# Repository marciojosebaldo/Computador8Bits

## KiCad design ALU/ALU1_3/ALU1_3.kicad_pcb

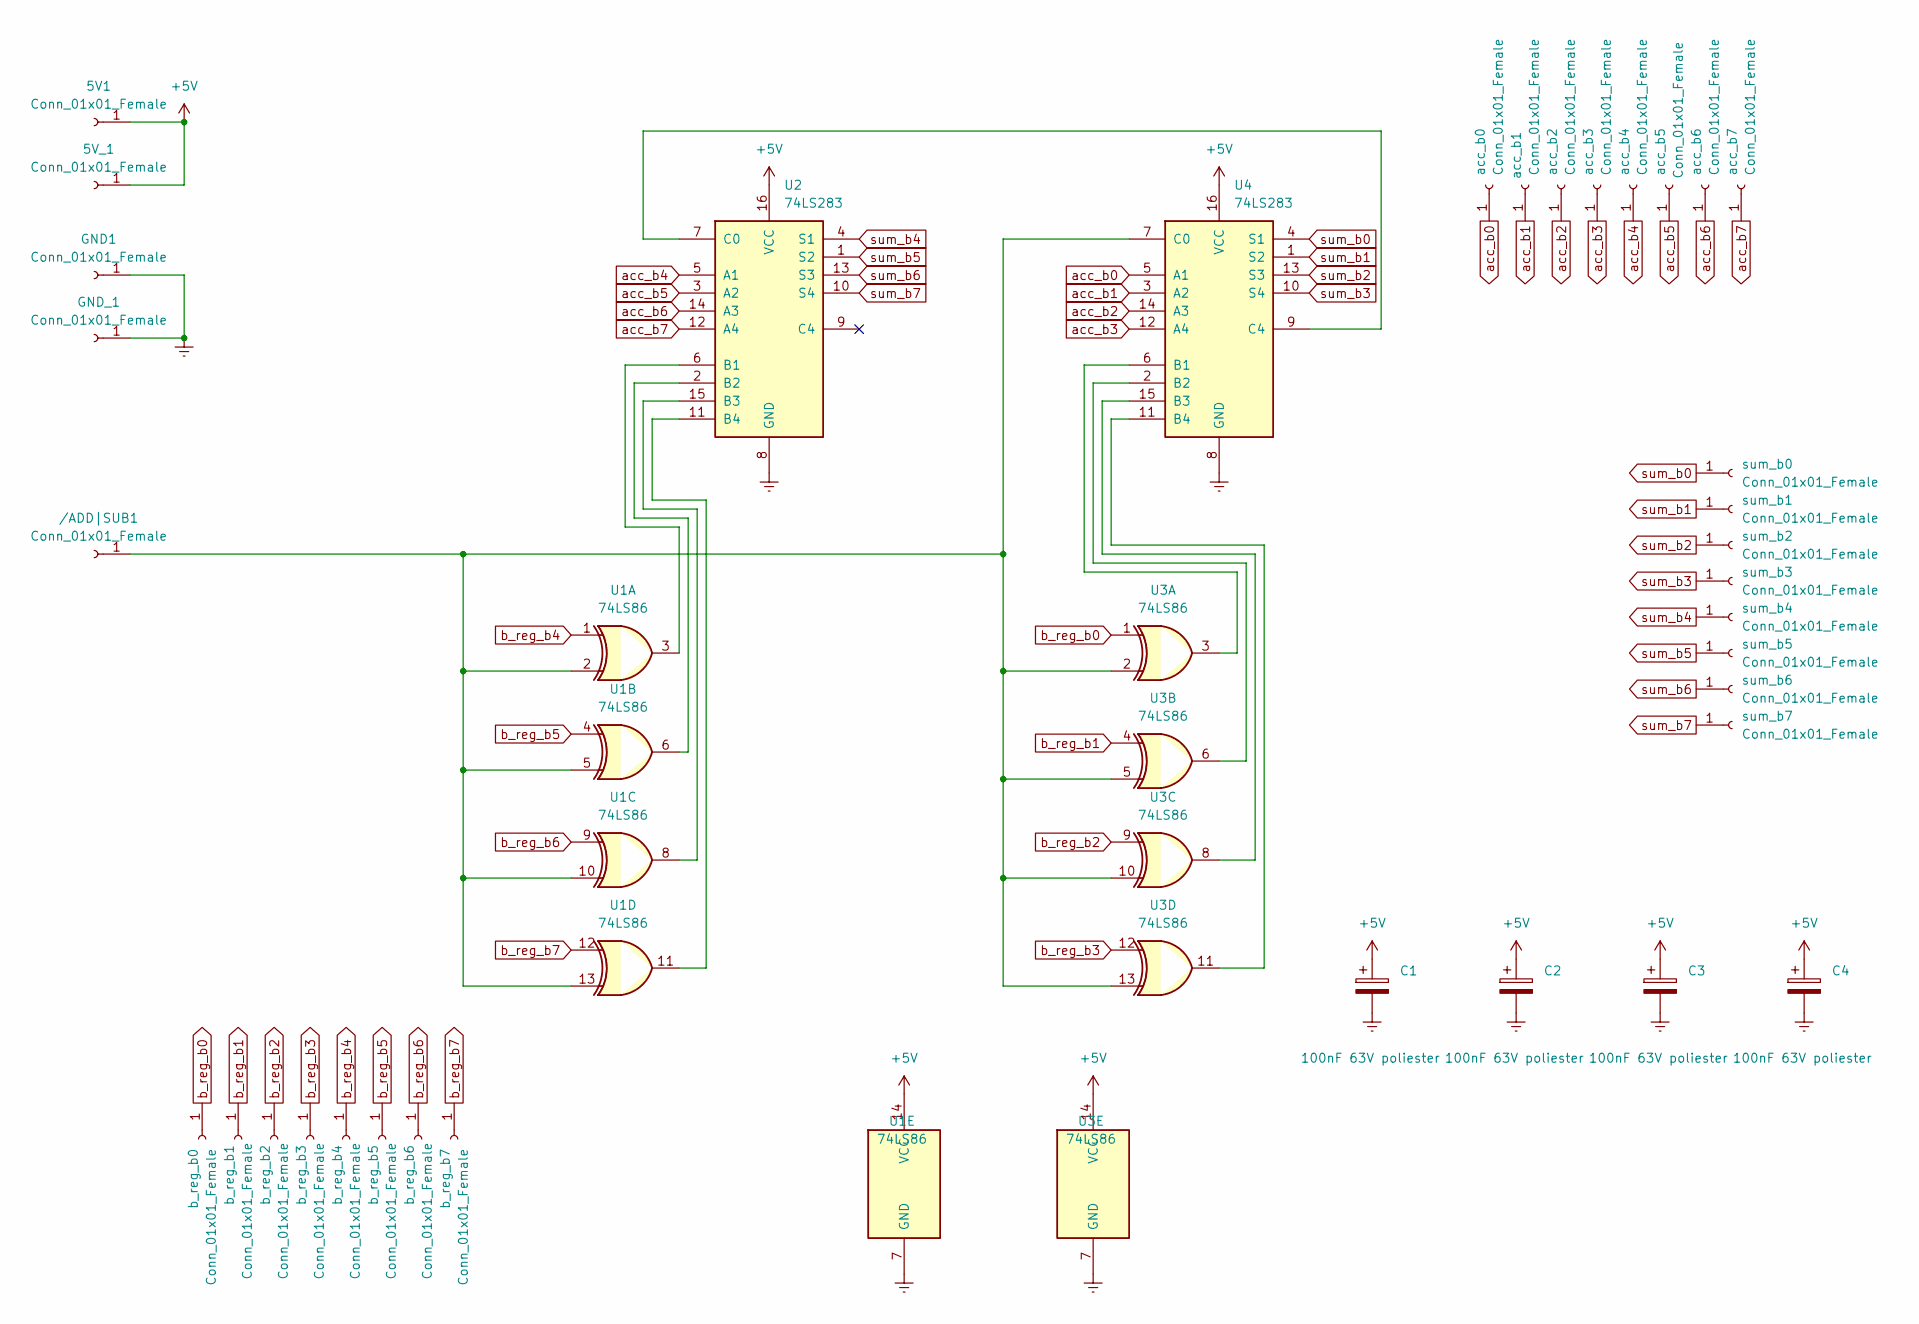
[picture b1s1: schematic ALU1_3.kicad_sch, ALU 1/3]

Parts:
5V1, 5V_1: Conn_01x01_Female; PinHeader_1x01_P1.00mm_Vertical
/ADD|SUB1: Conn_01x01_Female; PinHeader_1x01_P1.00mm_Vertical
C1, C2, C3, C4: 100nF 63V poliester; CP_Radial_D5.0mm_P2.00mm
GND1: Conn_01x01_Female; PinHeader_1x01_P1.00mm_Vertical
GND_1: Conn_01x01_Female; PinHeader_1x01_P1.00mm_Vertical
U1, U3: 74LS86; DIP-14_W7.62mm_Socket
U2, U4: 74LS283; DIP-16_W7.62mm_Socket
acc_b0, acc_b1, acc_b2, acc_b3, acc_b4, acc_b5, acc_b6, acc_b7: Conn_01x01_Female; PinHeader_1x01_P1.00mm_Vertical
b_reg_b0, b_reg_b1, b_reg_b2, b_reg_b3, b_reg_b4, b_reg_b5, b_reg_b6, b_reg_b7: Conn_01x01_Female; PinHeader_1x01_P1.00mm_Vertical
sum_b0, sum_b1, sum_b2, sum_b3, sum_b4, sum_b5, sum_b6, sum_b7: Conn_01x01_Female; PinHeader_1x01_P1.00mm_Vertical

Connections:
+5V: 5V1.1, 5V_1.1, C1.1, C2.1, C3.1, C4.1, U1.14 (VCC), U2.16 (VCC), U3.14 (VCC), U4.16 (VCC)
Earth: C1.2, C2.2, C3.2, C4.2, GND1.1, GND_1.1, U1.7 (GND), U2.8 (GND), U3.7 (GND), U4.8 (GND)
unnamed: /ADD|SUB1.1, U1.2, U1.5, U1.10, U1.13, U3.2, U3.5, U3.10, U3.13, U4.7 (C0)
unnamed: U1.3, U2.6 (B1)
unnamed: U1.6, U2.2 (B2)
unnamed: U1.8, U2.15 (B3)
unnamed: U1.11, U2.11 (B4)
unnamed: U2.7 (C0), U4.9 (C4)
unnamed: U3.3, U4.6 (B1)
unnamed: U3.6, U4.2 (B2)
unnamed: U3.8, U4.15 (B3)
unnamed: U3.11, U4.11 (B4)
acc_b0: U4.5 (A1), acc_b0.1
acc_b1: U4.3 (A2), acc_b1.1
acc_b2: U4.14 (A3), acc_b2.1
acc_b3: U4.12 (A4), acc_b3.1
acc_b4: U2.5 (A1), acc_b4.1
acc_b5: U2.3 (A2), acc_b5.1
acc_b6: U2.14 (A3), acc_b6.1
acc_b7: U2.12 (A4), acc_b7.1
b_reg_b0: U3.1, b_reg_b0.1
b_reg_b1: U3.4, b_reg_b1.1
b_reg_b2: U3.9, b_reg_b2.1
b_reg_b3: U3.12, b_reg_b3.1
b_reg_b4: U1.1, b_reg_b4.1
b_reg_b5: U1.4, b_reg_b5.1
b_reg_b6: U1.9, b_reg_b6.1
b_reg_b7: U1.12, b_reg_b7.1
sum_b0: U4.4 (S1), sum_b0.1
sum_b1: U4.1 (S2), sum_b1.1
sum_b2: U4.13 (S3), sum_b2.1
sum_b3: U4.10 (S4), sum_b3.1
sum_b4: U2.4 (S1), sum_b4.1
sum_b5: U2.1 (S2), sum_b5.1
sum_b6: U2.13 (S3), sum_b6.1
sum_b7: U2.10 (S4), sum_b7.1

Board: 2 copper layers, 37 parts (0 on the bottom side), 36 nets, no tracks yet.

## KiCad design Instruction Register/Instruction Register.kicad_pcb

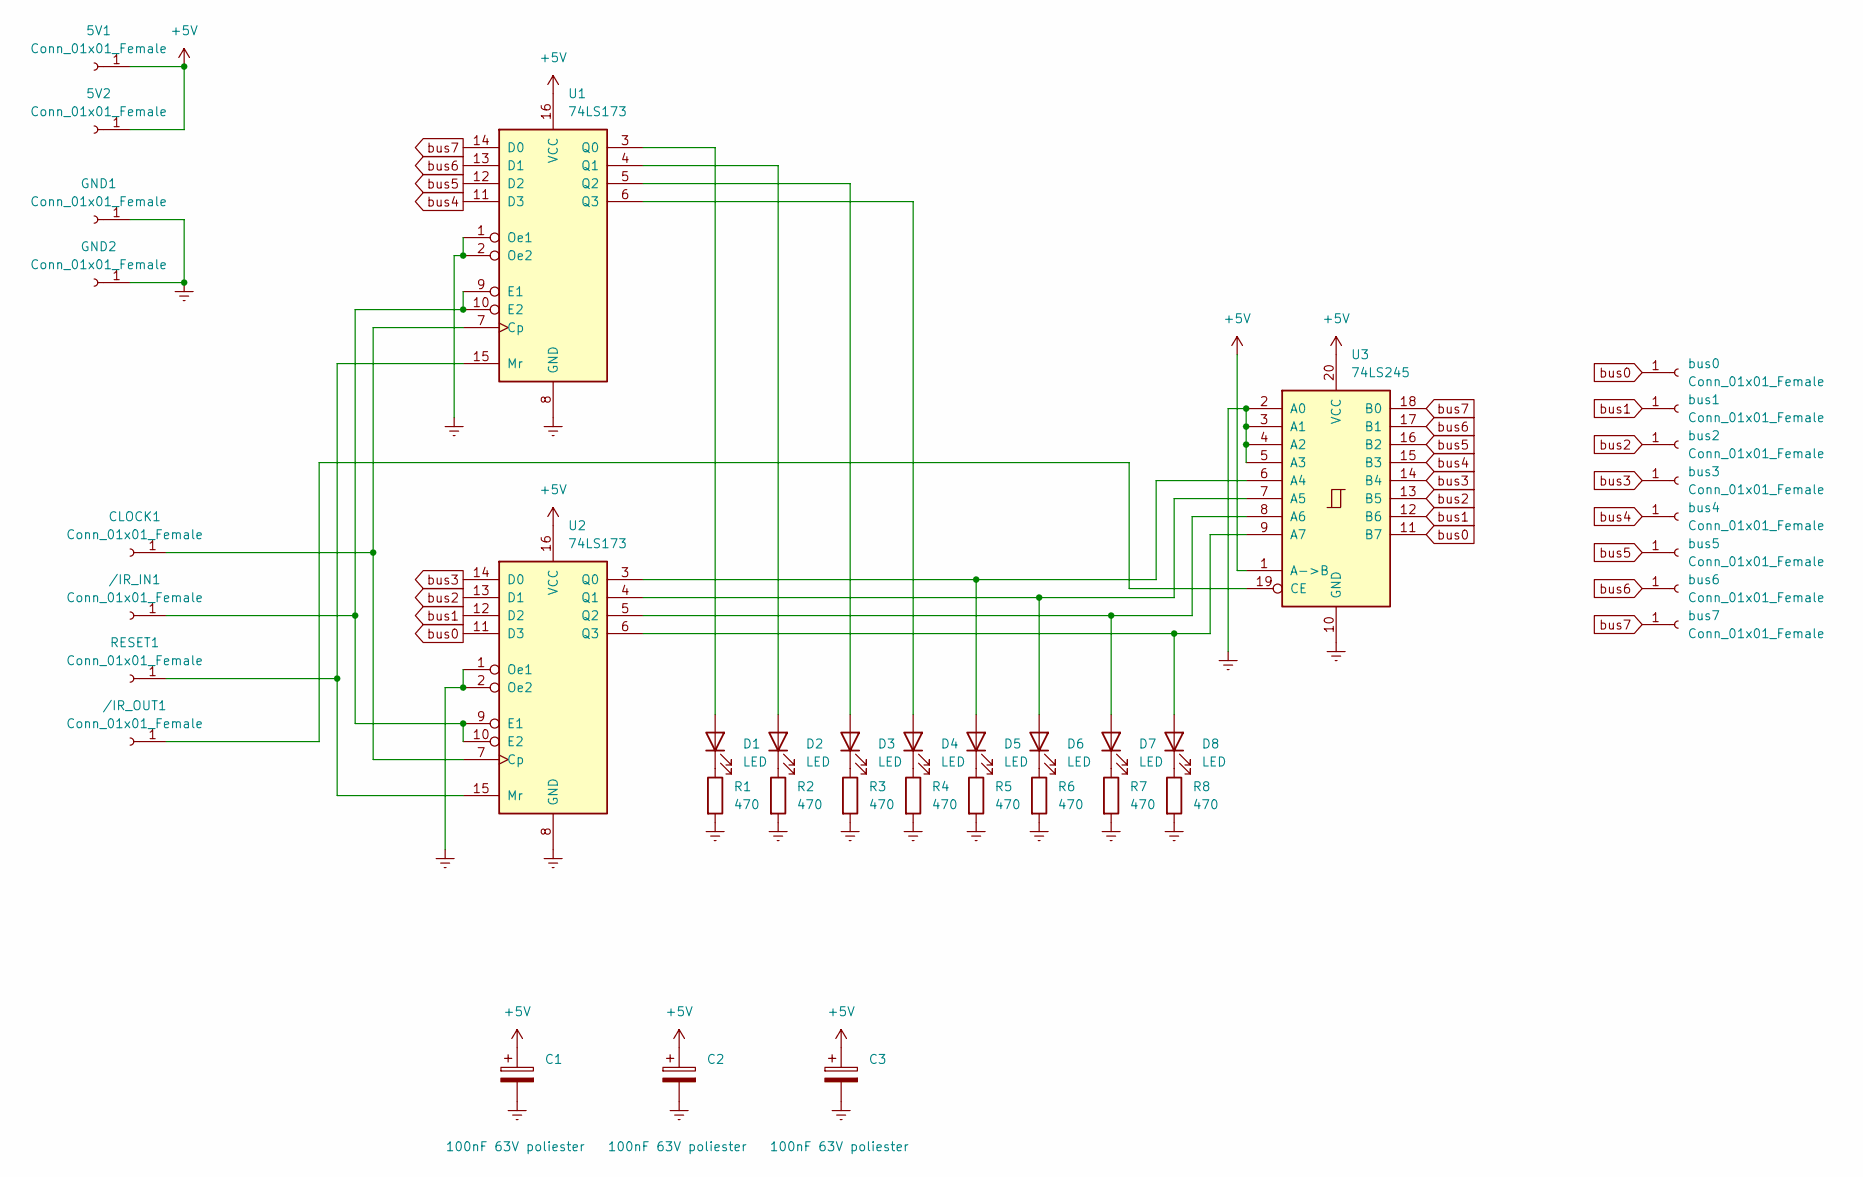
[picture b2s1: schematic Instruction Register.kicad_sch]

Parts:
5V1, 5V2: Conn_01x01_Female; PinHeader_1x01_P1.00mm_Vertical
/IR_IN1: Conn_01x01_Female; PinHeader_1x01_P1.00mm_Vertical
/IR_OUT1: Conn_01x01_Female; PinHeader_1x01_P1.00mm_Vertical
C1, C2, C3: 100nF 63V poliester; CP_Radial_D5.0mm_P2.00mm
CLOCK1: Conn_01x01_Female; PinHeader_1x01_P1.00mm_Vertical
D1, D2, D3, D4, D5, D6, D7, D8: LED; LED_D3.0mm
GND1, GND2: Conn_01x01_Female; PinHeader_1x01_P1.00mm_Vertical
R1, R2, R3, R4, R5, R6, R7, R8: 470; R_Axial_DIN0204_L3.6mm_D1.6mm_P7.62mm_Horizontal
RESET1: Conn_01x01_Female; PinHeader_1x01_P1.00mm_Vertical
U1, U2: 74LS173; DIP-16_W7.62mm_Socket
U3: 74LS245; DIP-20_W7.62mm_Socket
bus0, bus1, bus2, bus3, bus4, bus5, bus6, bus7: Conn_01x01_Female; PinHeader_1x01_P1.00mm_Vertical

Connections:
+5V: 5V1.1, 5V2.1, C1.1, C2.1, C3.1, U1.16 (VCC), U2.16 (VCC), U3.1 (A->B), U3.20 (VCC)
Earth: C1.2, C2.2, C3.2, GND1.1, GND2.1, R1.2, R2.2, R3.2, R4.2, R5.2, R6.2, R7.2, R8.2, U1.1 (Oe1), U1.2 (Oe2), U1.8 (GND), U2.1 (Oe1), U2.2 (Oe2), U2.8 (GND), U3.2 (A0), U3.3 (A1), U3.4 (A2), U3.5 (A3), U3.10 (GND)
unnamed: /IR_IN1.1, U1.9 (E1), U1.10 (E2), U2.9 (E1), U2.10 (E2)
unnamed: /IR_OUT1.1, U3.19 (CE)
unnamed: CLOCK1.1, U1.7 (Cp), U2.7 (Cp)
unnamed: D1.2 (A), U1.3 (Q0)
unnamed: D1.1 (K), R1.1
unnamed: D2.2 (A), U1.4 (Q1)
unnamed: D2.1 (K), R2.1
unnamed: D3.2 (A), U1.5 (Q2)
unnamed: D3.1 (K), R3.1
unnamed: D4.2 (A), U1.6 (Q3)
unnamed: D4.1 (K), R4.1
unnamed: D5.2 (A), U2.3 (Q0), U3.6 (A4)
unnamed: D5.1 (K), R5.1
unnamed: D6.2 (A), U2.4 (Q1), U3.7 (A5)
unnamed: D6.1 (K), R6.1
unnamed: D7.2 (A), U2.5 (Q2), U3.8 (A6)
unnamed: D7.1 (K), R7.1
unnamed: D8.2 (A), U2.6 (Q3), U3.9 (A7)
unnamed: D8.1 (K), R8.1
unnamed: RESET1.1, U1.15 (Mr), U2.15 (Mr)
bus0: U2.11 (D3), U3.11 (B7), bus0.1
bus1: U2.12 (D2), U3.12 (B6), bus1.1
bus2: U2.13 (D1), U3.13 (B5), bus2.1
bus3: U2.14 (D0), U3.14 (B4), bus3.1
bus4: U1.11 (D3), U3.15 (B3), bus4.1
bus5: U1.12 (D2), U3.16 (B2), bus5.1
bus6: U1.13 (D1), U3.17 (B1), bus6.1
bus7: U1.14 (D0), U3.18 (B0), bus7.1

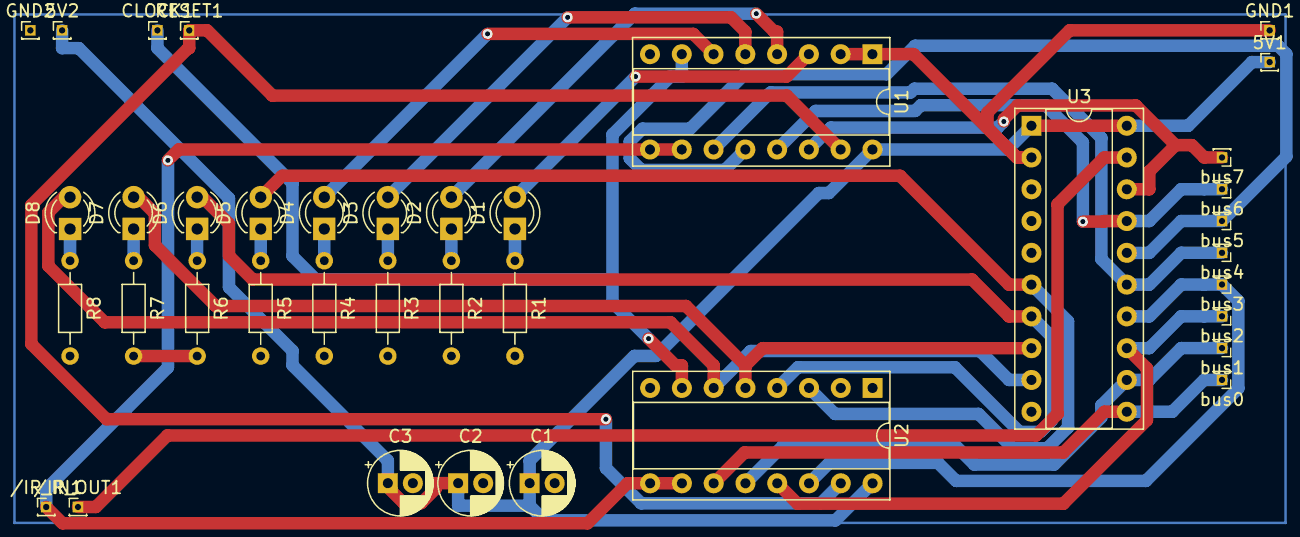
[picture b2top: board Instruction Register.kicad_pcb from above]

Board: 2 copper layers, 38 parts (0 on the bottom side), 30 nets.

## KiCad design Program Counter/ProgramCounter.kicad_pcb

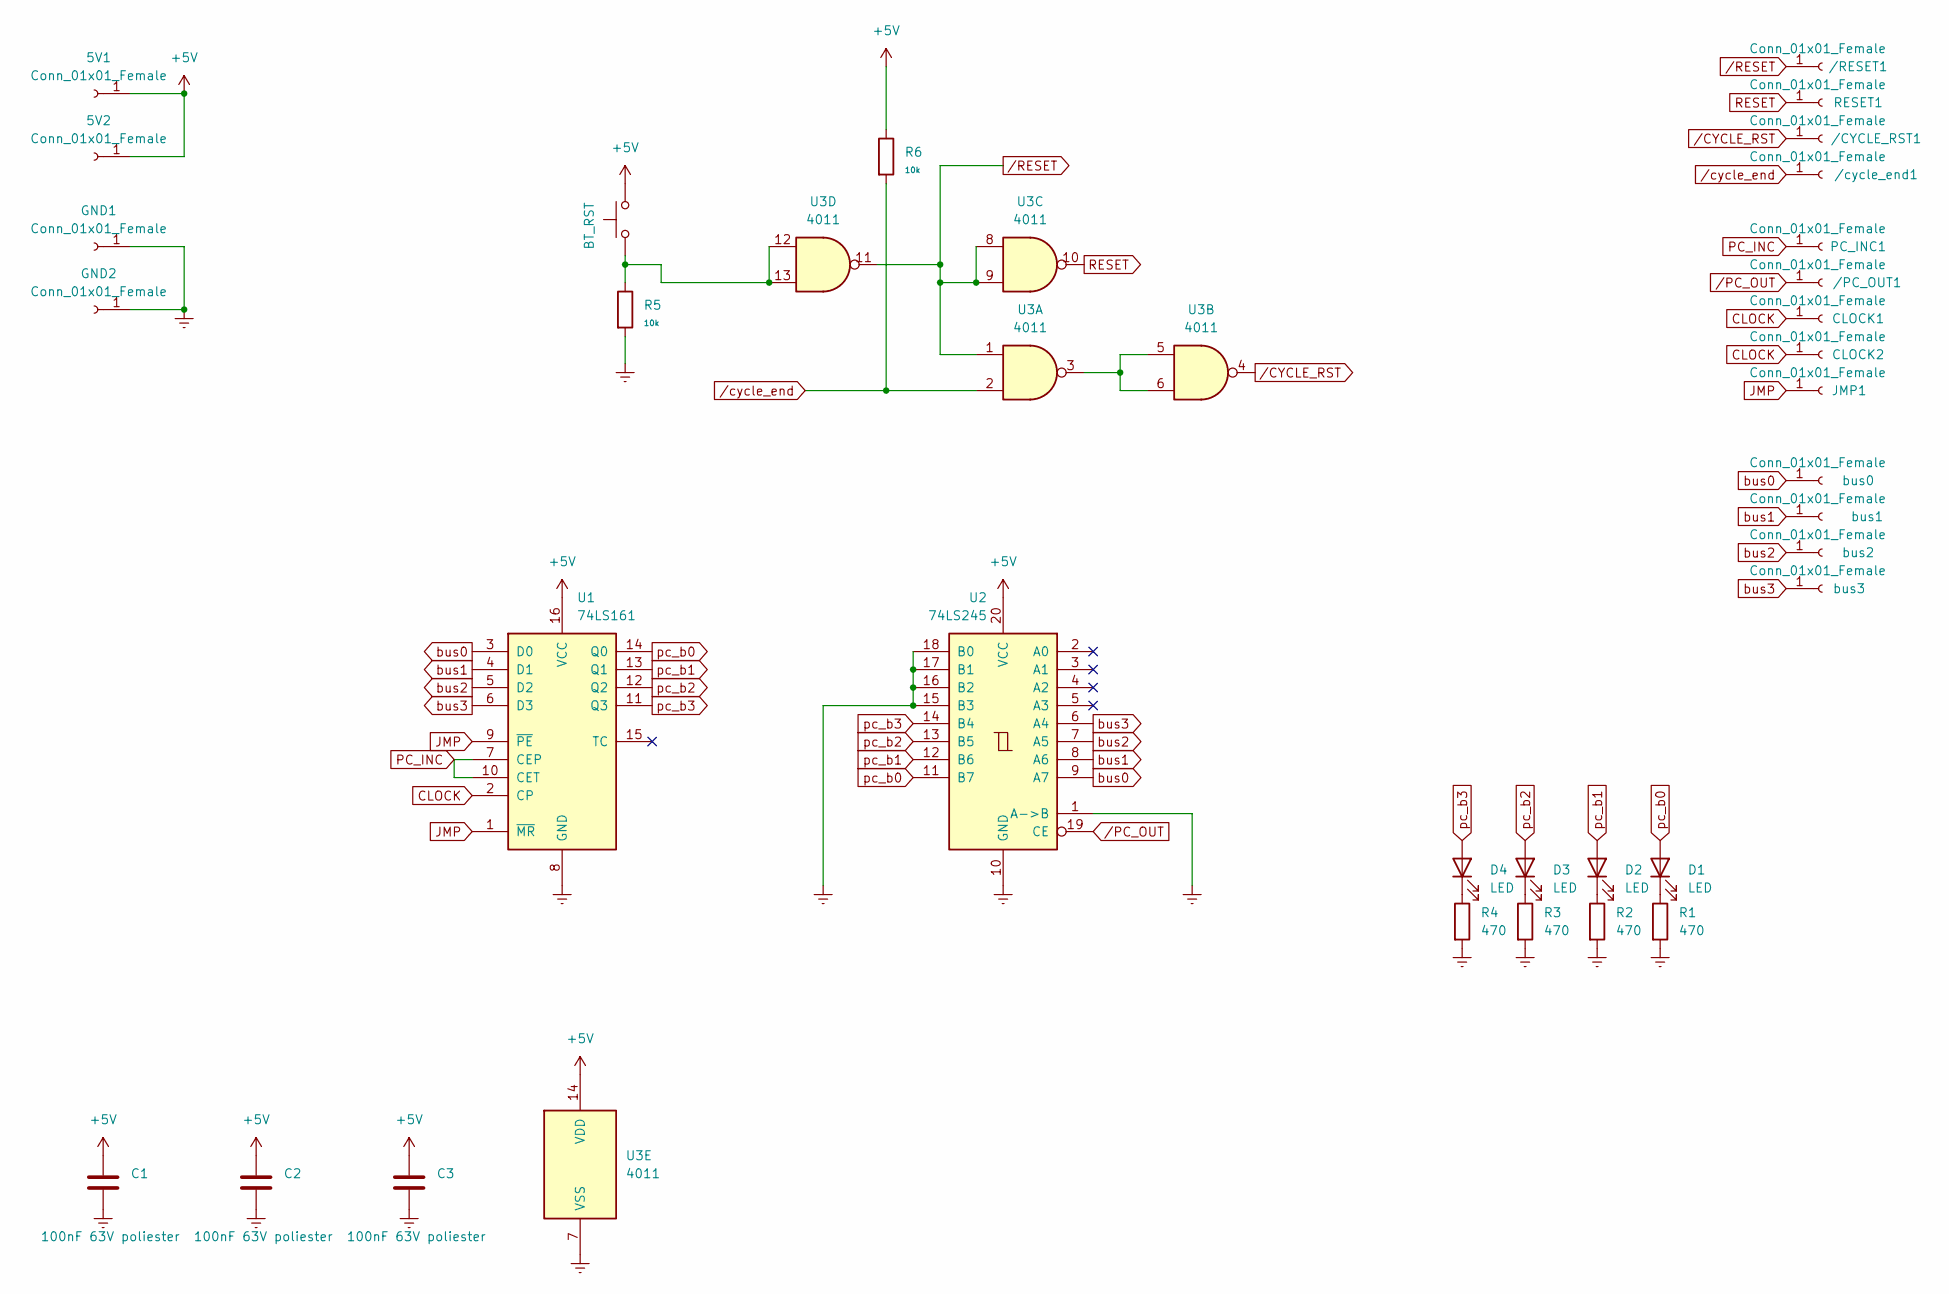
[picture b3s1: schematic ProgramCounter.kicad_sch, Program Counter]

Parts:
5V1, 5V2: Conn_01x01_Female; PinHeader_1x01_P1.00mm_Vertical
/CYCLE_RST1: Conn_01x01_Female; PinHeader_1x01_P1.00mm_Vertical
/PC_OUT1: Conn_01x01_Female; PinHeader_1x01_P1.00mm_Vertical
/RESET1: Conn_01x01_Female; PinHeader_1x01_P1.00mm_Vertical
/cycle_end1: Conn_01x01_Female; PinHeader_1x01_P1.00mm_Vertical
C1, C2, C3: 100nF 63V poliester; CP_Radial_D5.0mm_P2.00mm
CLOCK1, CLOCK2: Conn_01x01_Female; PinHeader_1x01_P1.00mm_Vertical
D1, D2, D3, D4: LED; LED_D3.0mm
GND1, GND2: Conn_01x01_Female; PinHeader_1x01_P1.00mm_Vertical
JMP1: Conn_01x01_Female; PinHeader_1x01_P1.00mm_Vertical
PC_INC1: Conn_01x01_Female; PinHeader_1x01_P1.00mm_Vertical
R1, R2, R3, R4: 470; R_Axial_DIN0204_L3.6mm_D1.6mm_P7.62mm_Horizontal
R5, R6: 10k; R_Axial_DIN0204_L3.6mm_D1.6mm_P7.62mm_Horizontal
RESET1: Conn_01x01_Female; PinHeader_1x01_P1.00mm_Vertical
SW1: BT_RST; SW_PUSH_6mm_H4.3mm
U1: 74LS161; DIP-16_W7.62mm
U2: 74LS245; DIP-20_W7.62mm
U3: 4011; DIP-14_W7.62mm_Socket
bus0, bus1, bus2, bus3: Conn_01x01_Female; PinHeader_1x01_P1.00mm_Vertical

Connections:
+5V: 5V1.1, 5V2.1, C1.1, C2.1, C3.1, R6.1, SW1.2, U1.16 (VCC), U2.20 (VCC), U3.14 (VDD)
CLOCK: CLOCK1.1, CLOCK2.1, U1.2 (CP)
Earth: C1.2, C2.2, C3.2, GND1.1, GND2.1, R1.2, R2.2, R3.2, R4.2, R5.2, U1.8 (GND), U2.1 (A->B), U2.10 (GND), U2.15 (B3), U2.16 (B2), U2.17 (B1), U2.18 (B0), U3.7 (VSS)
JMP: JMP1.1, U1.1 (~MR), U1.9 (~PE)
unnamed: D1.1 (K), R1.1
unnamed: D2.1 (K), R2.1
unnamed: D3.1 (K), R3.1
unnamed: D4.1 (K), R4.1
unnamed: R5.1, SW1.1, U3.12, U3.13
unnamed: U3.3, U3.5, U3.6
PC_INC: PC_INC1.1, U1.7 (CEP), U1.10 (CET)
RESET: RESET1.1, U3.10
bus0: U1.3 (D0), U2.9 (A7), bus0.1
bus1: U1.4 (D1), U2.8 (A6), bus1.1
bus2: U1.5 (D2), U2.7 (A5), bus2.1
bus3: U1.6 (D3), U2.6 (A4), bus3.1
pc_b0: D1.2 (A), U1.14 (Q0), U2.11 (B7)
pc_b1: D2.2 (A), U1.13 (Q1), U2.12 (B6)
pc_b2: D3.2 (A), U1.12 (Q2), U2.13 (B5)
pc_b3: D4.2 (A), U1.11 (Q3), U2.14 (B4)
/CYCLE_RST: /CYCLE_RST1.1, U3.4
/PC_OUT: /PC_OUT1.1, U2.19 (CE)
/RESET: /RESET1.1, U3.1, U3.8, U3.9, U3.11
/cycle_end: /cycle_end1.1, R6.2, U3.2

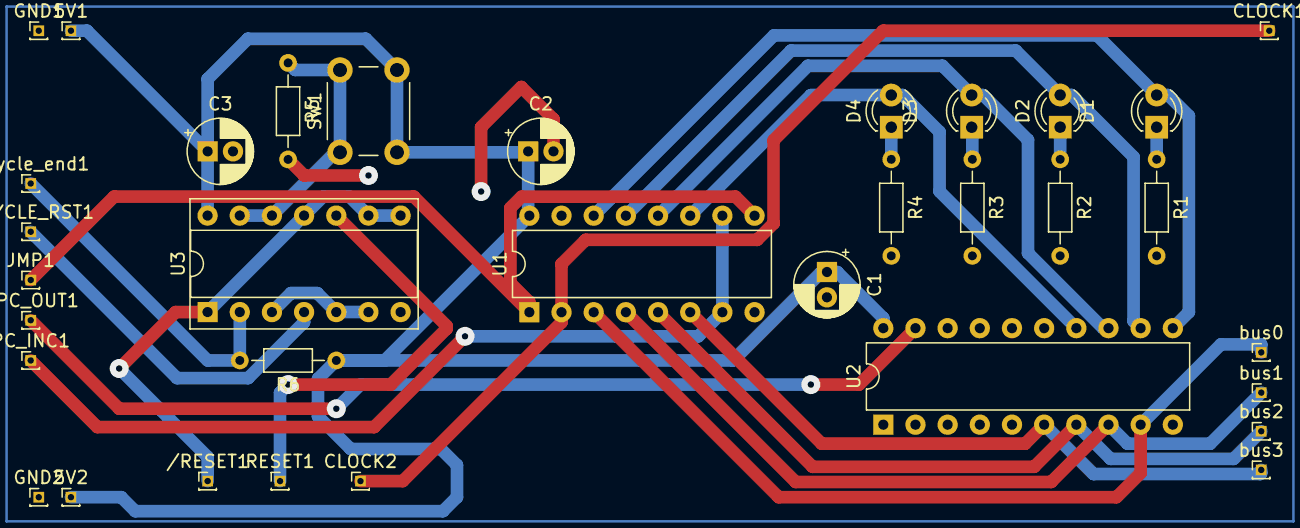
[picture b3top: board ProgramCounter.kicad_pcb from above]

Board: 2 copper layers, 34 parts (0 on the bottom side), 24 nets.

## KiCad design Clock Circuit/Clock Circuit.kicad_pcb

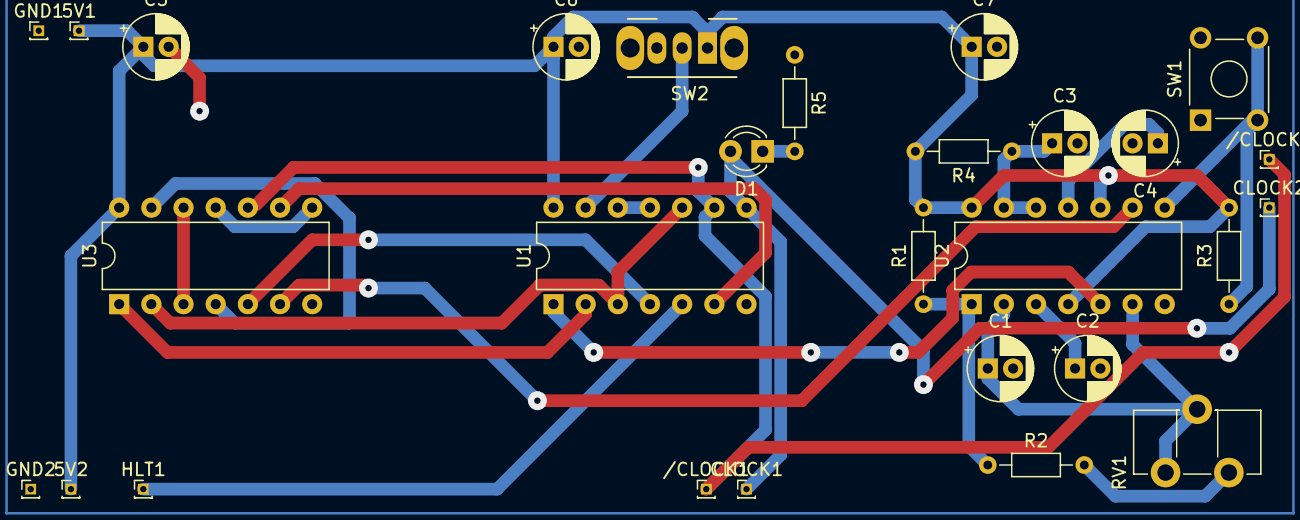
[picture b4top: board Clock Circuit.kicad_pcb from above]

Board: 2 copper layers, 28 parts (0 on the bottom side), 24 nets.

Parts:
5V1, 5V2: Conn_01x01_Female; PinHeader_1x01_P1.00mm_Vertical
/CLOCK1, /CLOCK2: Conn_01x01_Female; PinHeader_1x01_P1.00mm_Vertical
C1: 10uF 25V; CP_Radial_D5.0mm_P2.00mm
C2, C4: 10nF 63V poliester; CP_Radial_D5.0mm_P2.00mm
C3: 47nF 25V cerâmico; CP_Radial_D5.0mm_P2.00mm
C5, C6, C7: 100nF 63V poliester; CP_Radial_D5.0mm_P2.00mm
CLOCK1, CLOCK2: Conn_01x01_Female; PinHeader_1x01_P1.00mm_Vertical
D1: LED; LED_D3.0mm
GND1, GND2: Conn_01x01_Female; PinHeader_1x01_P1.00mm_Vertical
HLT1: Conn_01x01_Female; PinHeader_1x01_P1.00mm_Vertical
R1: 150; R_Axial_DIN0204_L3.6mm_D1.6mm_P7.62mm_Horizontal
R2: 10; R_Axial_DIN0204_L3.6mm_D1.6mm_P7.62mm_Horizontal
R3: 10k; R_Axial_DIN0204_L3.6mm_D1.6mm_P7.62mm_Horizontal
R4: 100k; R_Axial_DIN0204_L3.6mm_D1.6mm_P7.62mm_Horizontal
R5: 470; R_Axial_DIN0204_L3.6mm_D1.6mm_P7.62mm_Horizontal
RV1: 100k linear; Potentiometer_ACP_CA9-H5_Horizontal
SW1: SW_Push_Dual; SW_TH_Tactile_Omron_B3F-10xx
SW2: SW_SPDT; SW_CuK_OS102011MA1QN1_SPDT_Angled
U1: 4069; DIP-14_W7.62mm
U2: NE556; DIP-14_W7.62mm
U3: 4011; DIP-14_W7.62mm

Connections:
+5V: 5V1.1, 5V2.1, C5.1, C6.1, C7.1, R1.2, R3.2, R4.2, SW2.1 (A), U1.14 (VDD), U2.4 (R), U2.10 (R), U2.14 (VCC), U3.14 (VDD)
CLOCK: CLOCK1.1, CLOCK2.1, D1.2 (A), U1.8
CLOCK_AUTO: U1.2, U3.1
CLOCK_MAN: U2.9 (Q), U3.6
Earth: C1.2, C2.2, C3.2, C4.2, C5.2, C6.2, C7.2, GND1.1, GND2.1, R5.1, SW1.1, SW2.3 (C), U1.7 (VSS), U2.7 (GND), U3.7 (VSS)
HLT: HLT1.1, U1.5
unnamed: D1.1 (K), R5.2
unnamed: R2.2, RV1.3
unnamed: SW2.2 (B), U1.13
unnamed: U1.4, U3.5
unnamed: U1.6, U3.9
unnamed: U1.11, U1.12
unnamed: C2.1, U2.3 (CV)
unnamed: R1.1, R2.1, U2.1 (DIS)
unnamed: U1.1, U2.5 (Q)
unnamed: C1.1, RV1.1, RV1.2, U2.2 (THR), U2.6 (TR)
unnamed: C4.1, U2.11 (CV)
unnamed: C3.1, R4.1, U2.12 (THR), U2.13 (DIS)
unnamed: R3.1, SW1.2, U2.8 (TR)
unnamed: U3.8, U3.11
unnamed: U3.3, U3.12
unnamed: U3.4, U3.13
SELECT: U1.3, U1.10, U3.2
/CLOCK: /CLOCK1.1, /CLOCK2.1, U1.9, U3.10

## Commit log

2023-10-28 Add files via upload
    Falta o desenho da placa
2023-10-28 Add files via upload
    Falta o desenho da PCB
